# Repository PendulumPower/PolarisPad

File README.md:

# PolarisPad
A Macropad designed for space combat in games such as Star Citizen.<br>
Finished Device

Case:

Full Design:

PCB:

Schematic:

How to program:<br>
1. Connect the device to a computer using a usb-c data cable while pressing the boot button.<br>
2. Download the most recent .uf2 file from the releases.<br>
3. Drag and drop the .uf2 file into the folder for the device. It should close and reboot<br>
4. Done!<br>

BOM: <br>
-8 MX-Style switches <br>
-1 unsoldered Seeed XIAO RP2040 <br>
-8 through-hole 1N4148 Diodes <br>
-4 SK6812 MINI-E LEDs <br>
-1 EC11 Rotary encoders <br>
-1 0.91 inch OLED display

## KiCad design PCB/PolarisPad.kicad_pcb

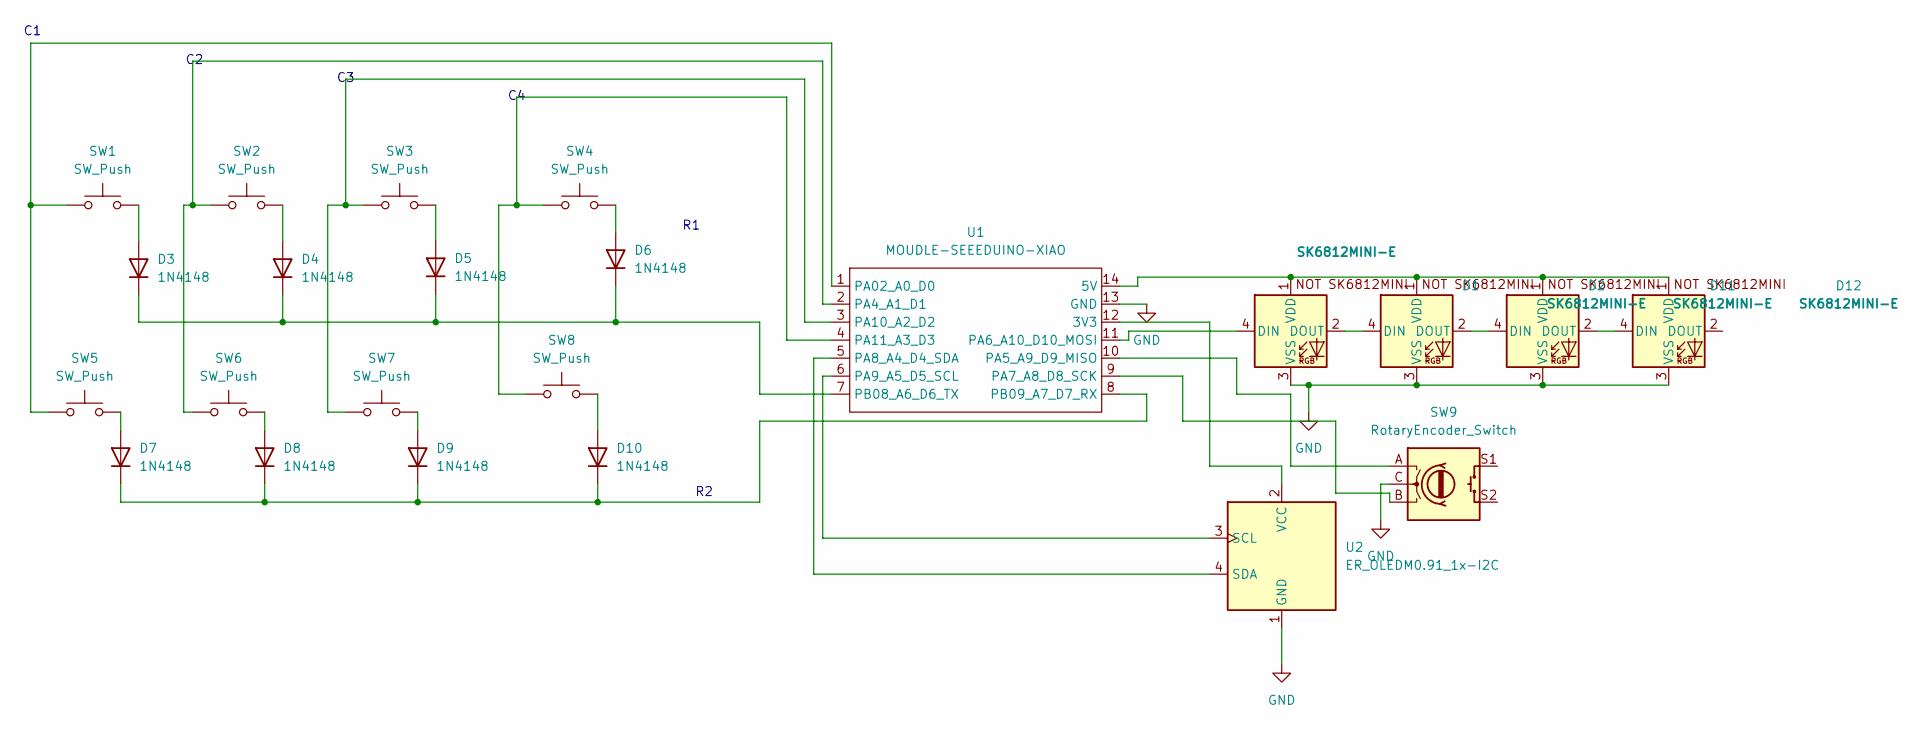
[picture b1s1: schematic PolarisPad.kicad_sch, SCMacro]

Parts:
D1, D2, D11, D12: SK6812MINI-E; SK6812MINI-E_fixed
D3, D4, D5, D6, D7, D8, D9, D10: 1N4148; D_DO-35_SOD27_P7.62mm_Horizontal
SW1, SW2, SW3, SW4, SW5, SW6, SW7, SW8: SW_Push; SW_Cherry_MX_1.00u_PCB
SW9: RotaryEncoder_Switch; RotaryEncoder_Alps_EC11E-Switch_Vertical_H20mm
U1: MOUDLE-SEEEDUINO-XIAO; XIAO-Generic-Hybrid-14P-2.54-21X17.8MM
U2: ER_OLEDM0.91_1x-I2C; FanPinHeader_1x04_P2.54mm_Vertical

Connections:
GND: D1.3 (VSS), D2.3 (VSS), D11.3 (VSS), D12.3 (VSS), SW9.C, U1.13 (GND), U2.1 (GND)
unnamed: D1.4 (DIN), U1.11 (PA6_A10_D10_MOSI)
unnamed: D1.2 (DOUT), D2.4 (DIN)
unnamed: D1.1 (VDD), D2.1 (VDD), D11.1 (VDD), D12.1 (VDD), U1.14 (5V)
unnamed: D3.2 (A), SW1.2
unnamed: D3.1 (K), D4.1 (K), D5.1 (K), D6.1 (K), U1.7 (PB08_A6_D6_TX)
unnamed: D4.2 (A), SW2.2
unnamed: D5.2 (A), SW3.2
unnamed: D6.2 (A), SW4.2
unnamed: D7.2 (A), SW5.2
unnamed: D8.2 (A), SW6.2
unnamed: D9.2 (A), SW7.2
unnamed: D10.2 (A), SW8.2
unnamed: D7.1 (K), D8.1 (K), D9.1 (K), D10.1 (K), U1.8 (PB09_A7_D7_RX)
unnamed: D2.2 (DOUT), D11.4 (DIN)
unnamed: D11.2 (DOUT), D12.4 (DIN)
unnamed: U1.12 (3V3), U2.2 (VCC)
unnamed: SW1.1, SW5.1, U1.1 (PA02_A0_D0)
unnamed: SW2.1, SW6.1, U1.2 (PA4_A1_D1)
unnamed: SW9.A, U1.10 (PA5_A9_D9_MISO)
unnamed: SW9.B, U1.9 (PA7_A8_D8_SCK)
unnamed: U1.5 (PA8_A4_D4_SDA), U2.4 (SDA)
unnamed: U1.6 (PA9_A5_D5_SCL), U2.3 (SCL)
unnamed: SW3.1, SW7.1, U1.3 (PA10_A2_D2)
unnamed: SW4.1, SW8.1, U1.4 (PA11_A3_D3)

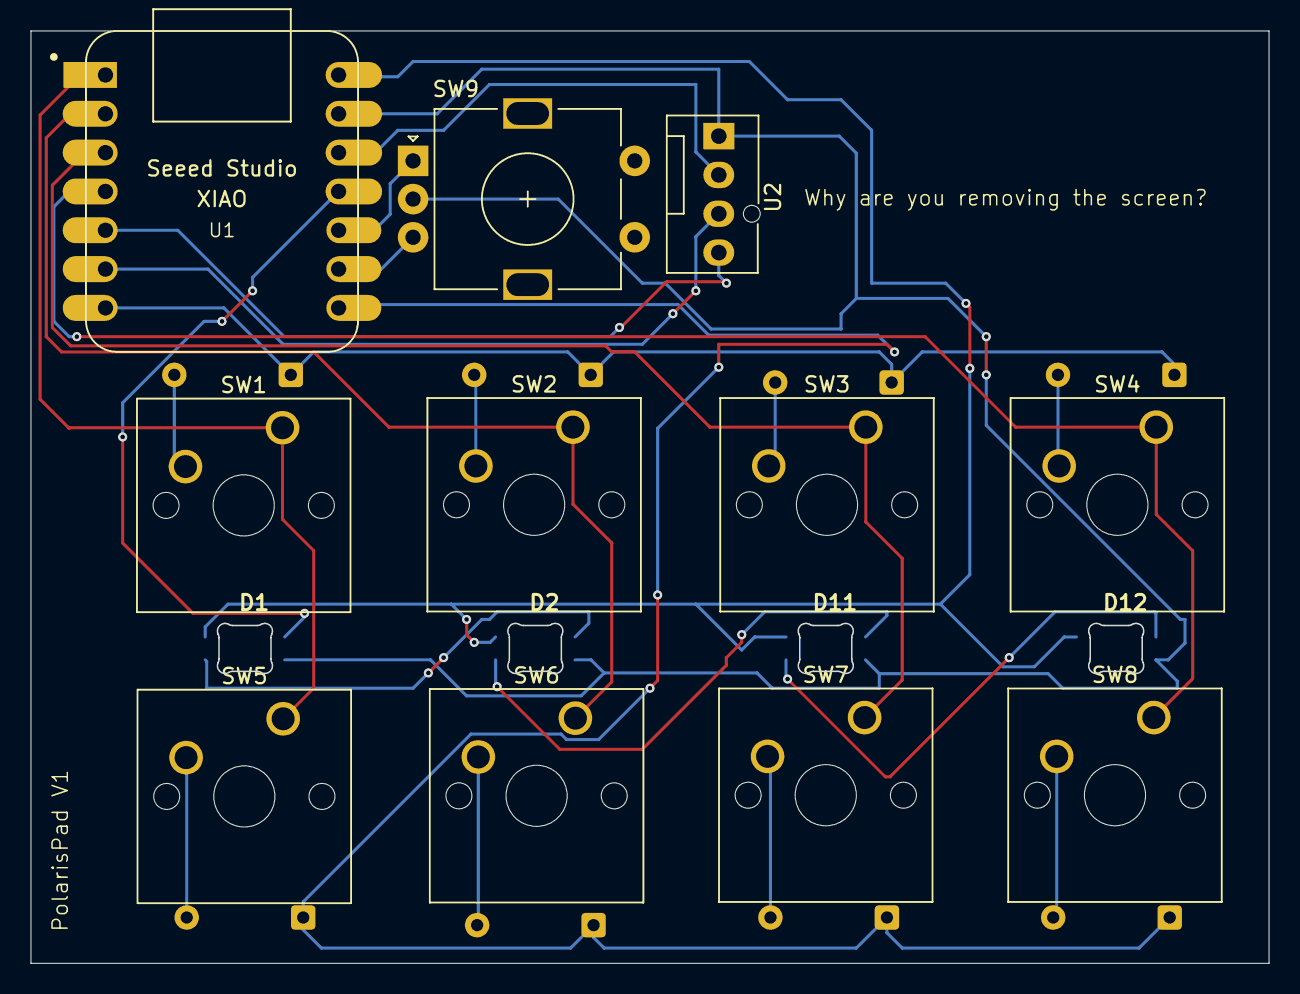
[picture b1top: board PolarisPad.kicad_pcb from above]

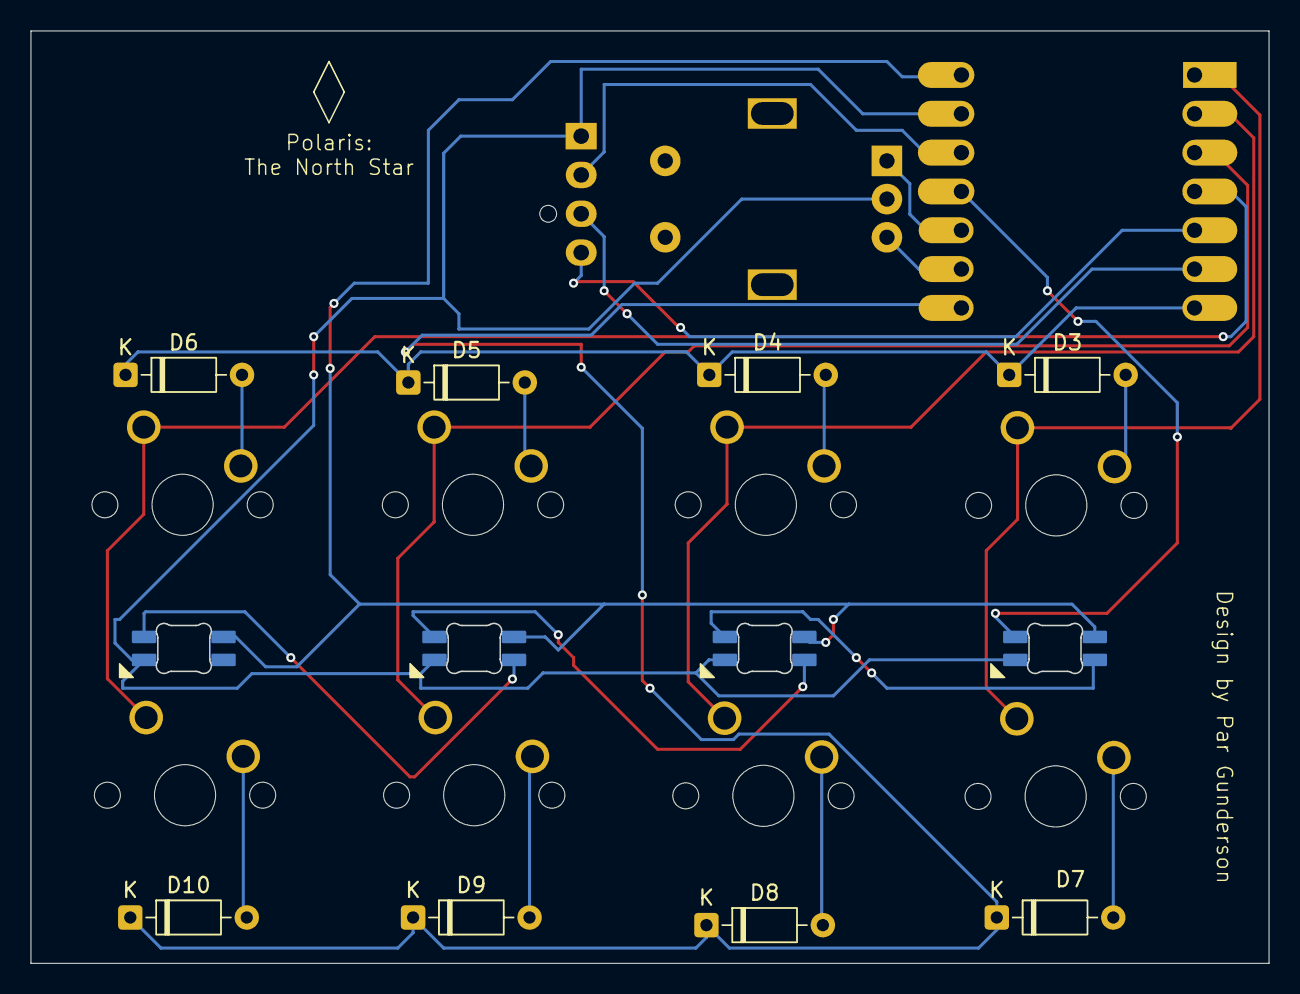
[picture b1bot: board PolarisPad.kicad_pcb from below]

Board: 2 copper layers, 81.0 x 61.0 mm, 23 parts (8 on the bottom side), 25 nets.
